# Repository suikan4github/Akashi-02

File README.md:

# Akashi-02
A test Jig for Murasaki-Library. Tested with audio codec board UMB-AD1361A.

## Functionality
This board is designed to test the audio interface functionality of the STM32 series MCU. The connectors can be directly mounted on the Nucleo 144 series board. With this board, the following audio interface can be tested :
- SAI peripheral (STM32F722, F746, H743)
- Simplex I2S peripheral (STM32F722, F746)
- Duplex I2S peripheral (STM32H743)

These functionalities are tested with following codec board as with I2C control line. 
- [UMB-ADAU1361A](http://dsps.shop-pro.jp/?pid=82798273)

## Development
- [KiCad 5.1](http://kicad.org/blog/2019/03/KiCad-5.1.0-Release/)
- [Nucleo F722ZE](https://www.st.com/en/evaluation-tools/nucleo-f722ze.html)
- [Nucleo F746ZG](https://www.st.com/ja/evaluation-tools/nucleo-f746zg.html)
- [Nucleo H743ZI](https://www.st.com/ja/evaluation-tools/nucleo-h743zi.html)

The schematics [can be donwloaded](docs/Akashi-02.pdf) as PDF format. 

## I2C address
By default, the I2C device address are fixed as ***0x38*** ( 7bit address ). If you want to change, you should modify the short bridge J2-J5 as following :
- J2 : Open by cutting the pattern.
- J3 : Close by soldering.
- J4 : Open by cutting the pattern.
- J5 : Close by soldering.

By above modification , the address can be controlled by GPIO PB12 and PA15. The address can be determined as following :

| b6 | b5 | b4 | b3 | b2 | b1    | b0   |
-----|----|----|----|----|-------|---- 
| 0  | 1  | 1  | 1  | 0  | PB12  | PA15 |

## Audio Port selection
This board allow to use SAI or I2S ( Both simplex and duplex). By default, ***Only SAI connection*** is allowed. The configuration of the board is as following : 

| Port | JP1     | JP6     | R5        |
-------|---------|---------|-----------
| SAI  | Opened  | Closed  | Removed   |
| I2S  | Closed  | Opened  | Removed   |
| Both | Opened  | Closed  | Installed |

"Both" is not recommended.

## Usage
To clone this project, follow :
```
git clone repository-of-this-project
git submodule update
```

The sample programs are published as [murasaki_samples_audio](https://github.com/suikan4github/murasaki_samples_audio) repositories. 

 To use these repository, follow the sequence :
 1. Clone the murasaki_samples_audio repository
 1. Import to CubeIDE

## License
This PCB design is released under the [Creative Commons Attribution 4.0 International license](https://creativecommons.org/licenses/by/4.0/). You are welcome to use this design for commercial purposes.

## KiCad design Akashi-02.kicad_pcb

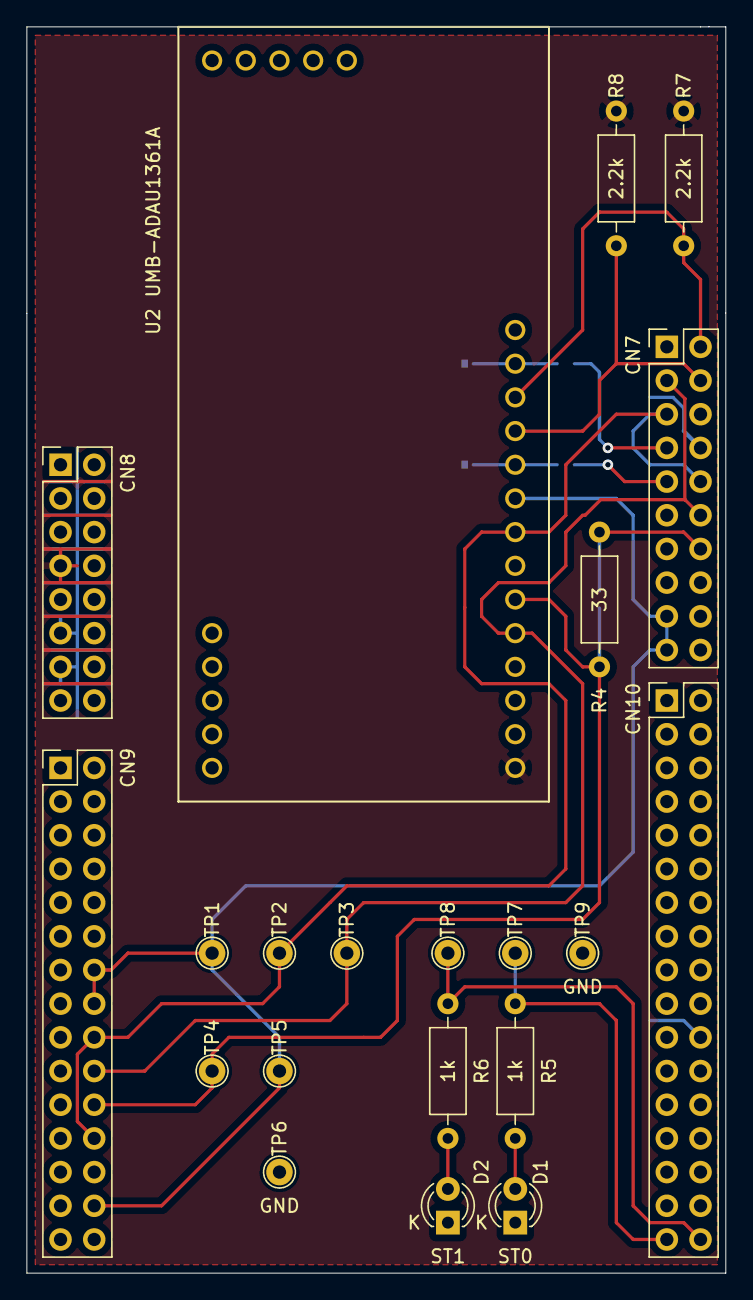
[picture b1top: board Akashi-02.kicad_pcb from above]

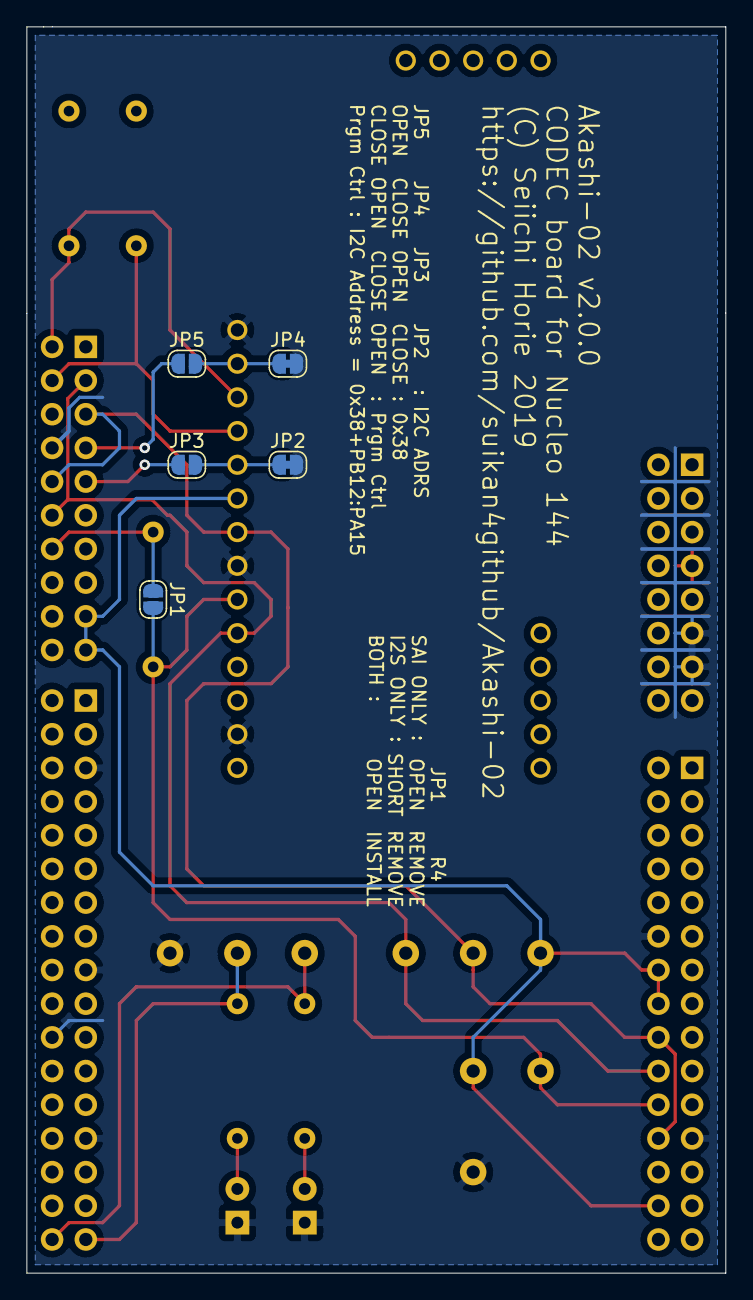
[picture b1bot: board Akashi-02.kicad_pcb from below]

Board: 2 copper layers, 52.7 x 94.0 mm, 26 parts (5 on the bottom side), 17 nets.

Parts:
CN7: Conn_02x10_Odd_Even; PinHeader_2x10_P2.54mm_Vertical
CN8: Conn_02x08_Odd_Even; PinHeader_2x08_P2.54mm_Vertical
CN9: Conn_02x15_Odd_Even; PinHeader_2x15_P2.54mm_Vertical
CN10: Conn_02x17_Odd_Even; PinHeader_2x17_P2.54mm_Vertical
D1, D2: LED; LED_D3.0mm_Clear
JP1, JP3, JP5: SolderJumper_2_Open; SolderJumper-2_P1.3mm_Open_RoundedPad1.0x1.5mm
JP2, JP4: SolderJumper_2_Bridged; SolderJumper-2_P1.3mm_Bridged_RoundedPad1.0x1.5mm
R4: 33; R_Axial_DIN0207_L6.3mm_D2.5mm_P10.16mm_Horizontal
R5, R6: 1k; R_Axial_DIN0207_L6.3mm_D2.5mm_P10.16mm_Horizontal
R7, R8: 2.2k; R_Axial_DIN0207_L6.3mm_D2.5mm_P10.16mm_Horizontal
TP1: FS_A; TestPoint_THTPad_D2.0mm_Drill1.0mm
TP2: SCK_A; TestPoint_THTPad_D2.0mm_Drill1.0mm
TP3: ADC; TestPoint_THTPad_D2.0mm_Drill1.0mm
TP4: DAC; TestPoint_THTPad_D2.0mm_Drill1.0mm
TP5: FS_B; TestPoint_THTPad_D2.0mm_Drill1.0mm
TP6, TP9: GND; TestPoint_THTPad_D2.0mm_Drill1.0mm
TP7: ST0; TestPoint_THTPad_D2.0mm_Drill1.0mm
TP8: ST1; TestPoint_THTPad_D2.0mm_Drill1.0mm
U2: UMB-ADAU1361A

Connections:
+3V3: CN8.7, R7.1, R8.1, U2.1
/ADDR0: CN7.9, JP3.1
/ADDR1: CN7.7, JP5.1
/DAC_SD: CN9.22, JP1.2, R4.1, TP4.1, U2.6
/I2C1_SCL: CN7.2, R7.2, U2.12
/I2C1_SDA: CN7.4, R8.2, U2.11
/I2S1_CK: CN7.5, CN7.10, CN9.18, CN9.24, TP2.1, U2.8
/I2S1_SD: CN7.14, JP1.1, R4.2
/I2S1_SDI: CN7.3, CN7.12, CN9.20, TP3.1, U2.5
/I2S1_WS: CN7.17, CN7.19, CN9.14, CN9.16, CN9.28, TP1.1, TP5.1, U2.9
/ST0: CN10.33, R5.1, TP7.1
/ST1: CN10.34, R6.1, TP8.1
GND: CN7.8, CN8.11, CN8.13, CN9.12, CN9.23, CN10.5, CN10.17, CN10.22, CN10.27, D1.1, D2.1, JP2.2, JP4.2, TP6.1, TP9.1, U2.2, U2.7, U2.14
unnamed: D1.2, R5.2
unnamed: D2.2, R6.2
unnamed: JP2.1, JP3.2, U2.10
unnamed: JP4.1, JP5.2, U2.13

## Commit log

2019-03-28 Moved from old project
2019-03-31 Added README.md
    Prepare to be public, after the submittion of gerber to fab.
2019-04-14 Add CHANGELOG
2019-04-14 Added link to tag v0.0.0
2019-04-14 Change drill size of the test point
    Issue : Test pin hole is too small #1
    https://github.com/suikan4github/Akashi-02/issues/1
2019-04-14 Change size of the COPYRIGHT
    Issue : Copy right is too small #2
    https://github.com/suikan4github/Akashi-02/issues/2
2019-04-14 Change drill size of the modules
    Issue 3 : Update footprint
    https://github.com/suikan4github/Akashi-02/issues/3
2019-04-14 Generate gerber
2019-04-14 Added Schematics
2019-04-17 Fixed codec identification
    Issue : CODEC identification is wrong. #4
    https://github.com/suikan4github/Akashi-02/issues/4
2019-04-17 Record the change of Issue #4
2019-05-12 Fix the codec identification
    Issue : CODEC identification is wrong. #4
    https://github.com/suikan4github/Akashi-02/issues/4
2019-10-26 Change the board function and figure.
    Issue 5 : U2 Pin4 is set ground by mistake
    https://github.com/suikan4github/Akashi-02/issues/5
    Issue 6 : Remove SSM2603 support
    https://github.com/suikan4github/Akashi-02/issues/6
    Issue 7 : Remove SPI support
    https://github.com/suikan4github/Akashi-02/issues/7
2019-10-27 Added TOL-POT4 connector. Preparing to release.
    - Updated README.md
    - Updated pin-config.png
    - Updated gerber
    - Updated schematics in PDF
2019-10-31 Ordered version 2.0.0
2019-11-03 Fixed table format bug in readme.
2019-11-03 Fixed table format bug
2019-11-03 Emphasized default value.
2019-12-11 Modified readme to prepare the release.
2019-12-11 Prepare to release
2019-12-11 Added phot of the board.
2019-12-29 Change project to stand alone.
    Issue #11 : Make external library access to local
    https://github.com/suikan4github/Akashi-02/issues/11
2019-12-29 Update REAMDE
    Explanation of submodule.
2021-11-10 Update README.md
    https://forum.kicad.info/t/warning-avoid-all-links-to-kicad-pcb-org-use-kicad-org/31521
